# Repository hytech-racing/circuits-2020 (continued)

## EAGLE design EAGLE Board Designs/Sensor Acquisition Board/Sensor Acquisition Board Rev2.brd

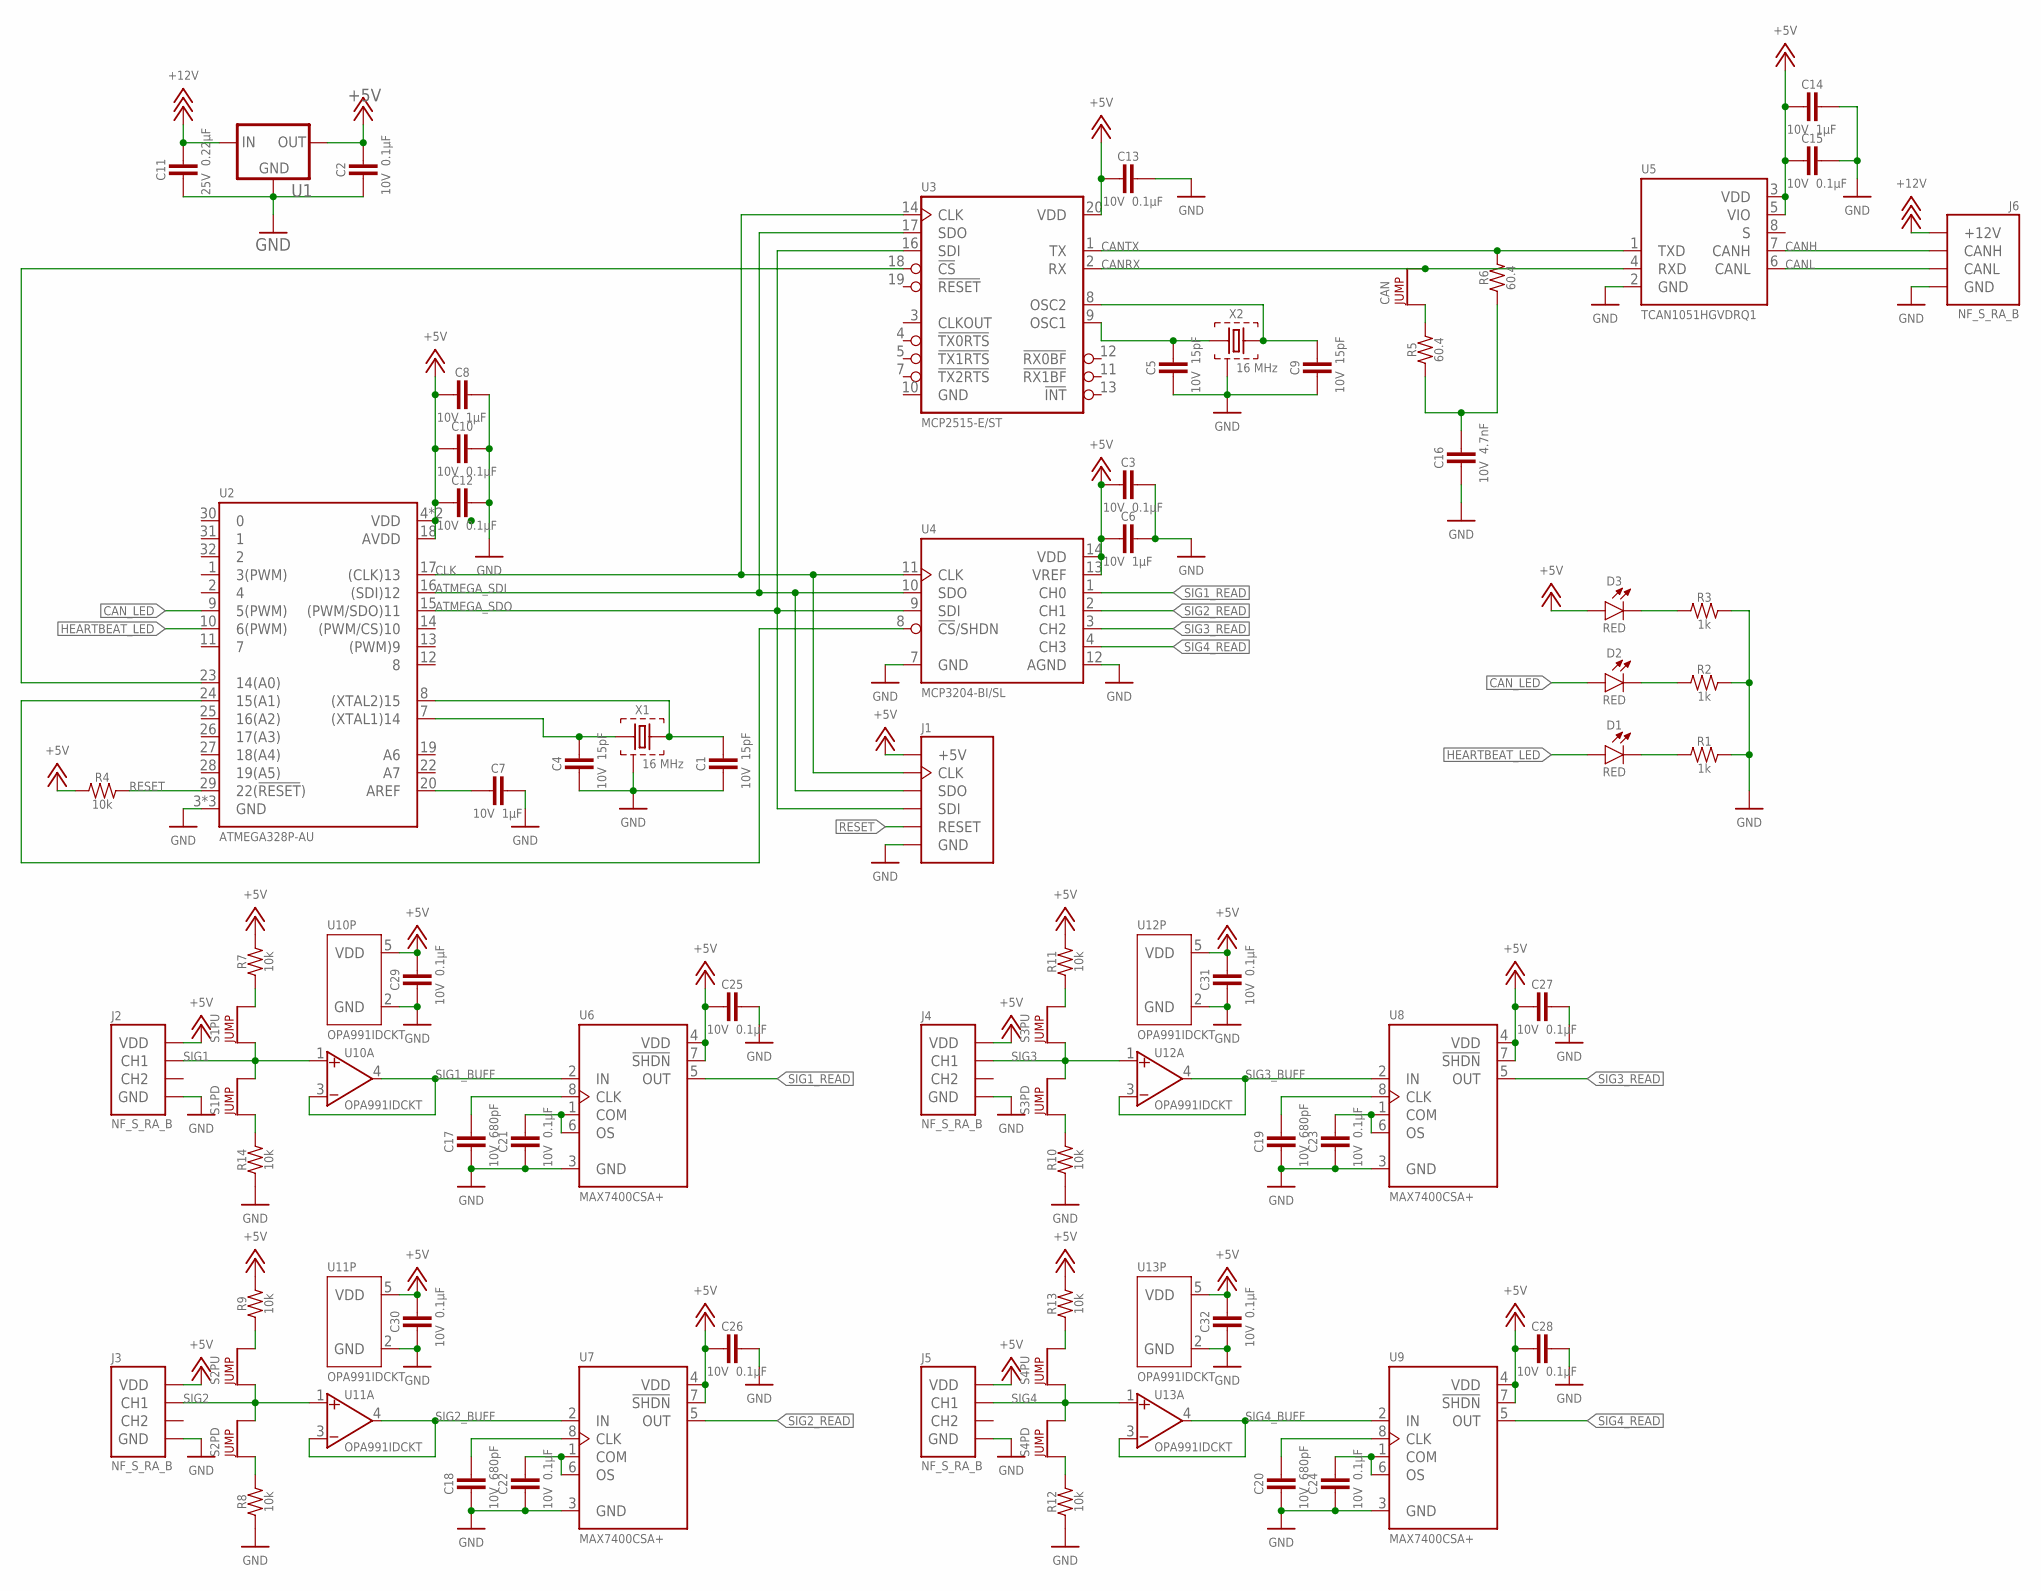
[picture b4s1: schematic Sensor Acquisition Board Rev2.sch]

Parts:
C1, C4, C5, C9: CAPACITOR_0603_10V_15PF; 0603-CAP
C2, C3, C10, C12, C13, C15, C21, C22, C23, C24, C25, C26, C27, C28, C29, C30, C31, C32: CAPACITOR_0603_10V_0.1UF; 0603-CAP
C6, C7, C8, C14: CAPACITOR_0603_10V_1UF; 0603-CAP
C11: CAPACITOR_0603_25V_0.22UF; 0603-CAP
C16: CAPACITOR_0603_10V_4.7NF; 0603-CAP
C17, C18, C19, C20: CAPACITOR_0603_10V_680PF; 0603-CAP
CAN: JUMPER_1X02_; 1X02
D1, D2, D3: LED_0603_RED; 0603-LED
J1: CONNECTOR-AVR-ISP__; 2X03
J2, J3, J4, J5: CONNECTOR-SENSOR_NF_S_RA_BLACK; MOLEX_NANOFIT_SMD_RIGHTANGLE_04
J6: CONNECTOR-CAN_NF_S_RA_BLACK; MOLEX_NANOFIT_SMD_RIGHTANGLE_04
R1, R2, R3: RESISTOR_0603_1K; 0603-RES
R4, R7, R8, R9, R10, R11, R12, R13, R14: RESISTOR_0603_10K; 0603-RES
R5, R6: RESISTOR_0603_60.4; 0603-RES
S1PD, S1PU, S2PD, S2PU, S3PD, S3PU, S4PD, S4PU: JUMPER_1X02_; 1X02
U1: LM340; SOT223
U2: ATMEGA328P-AU; TQFP-32
U3: MCP2515; TSSOP-20
U4: MCP3204; SOIC-14
U5: CAN_TRANSCIEVER_TCAN1051HQV-Q1; SOIC-08
U6, U7, U8, U9: MAX7400; SOIC-08
U10, U11, U12, U13: OPAMP_1_CHANNEL_OPA991; SC-70-5
X1, X2: CRYSTAL16MHZ; ABM3B

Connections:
+5V: C2.1, C3.2, C6.2, C8.2, C10.2, C12.2, C13.2, C14.2, C15.2, C25.2, C26.2, C27.2, C28.2, C29.1, C30.1, C31.1, C32.1, D3.2 (A), J1.2 (+5V), J2.1 (VDD), J3.1 (VDD), J4.1 (VDD), J5.1 (VDD), R4.1, R7.2, R9.2, R11.2, R13.2, U1.3 (OUT), U2.4 (VDD), U2.6 (VDD), U2.18 (AVDD), U3.20 (VDD), U4.13 (VREF), U4.14 (VDD), U5.3 (VDD), U5.5 (VIO), U6.4 (VDD), U6.7 (!SHDN), U7.4 (VDD), U7.7 (!SHDN), U8.4 (VDD), U8.7 (!SHDN), U9.4 (VDD), U9.7 (!SHDN), U10.5 (VDD), U11.5 (VDD), U12.5 (VDD), U13.5 (VDD)
+12V: C11.1, J6.1 (+12V), U1.1 (IN)
ATMEGA_CS: U2.24 (15(A1)), U4.8 (!CS!/SHDN)
ATMEGA_SDI: J1.4 (SDO), U2.16 ((SDI)12), U3.17 (SDO), U4.10 (SDO)
ATMEGA_SDO: J1.1 (SDI), U2.15 ((PWM/SDO)11), U3.16 (SDI), U4.9 (SDI)
CANH: J6.4 (CANH), U5.7 (CANH)
CANL: J6.3 (CANL), U5.6 (CANL)
CANRX: CAN.2, U3.2 (RX), U5.4 (RXD)
CANTX: R6.2, U3.1 (TX), U5.1 (TXD)
CAN_LED: D2.2 (A), U2.9 (5(PWM))
CLK: J1.3 (CLK), U2.17 ((CLK)13), U3.14 (CLK), U4.11 (CLK)
GND: C1.2, C2.2, C3.1, C4.2, C5.2, C6.1, C7.1, C8.1, C9.2, C10.1, C11.2, C12.1, C13.1, C14.1, C15.1, C16.2, C17.2, C18.2, C19.2, C20.2, C21.2, C22.2, C23.2, C24.2, C25.1, C26.1, C27.1, C28.1, C29.2, C30.2, C31.2, C32.2, J1.6 (GND), J2.2 (GND), J3.2 (GND), J4.2 (GND), J5.2 (GND), J6.2 (GND), R1.2, R2.2, R3.2, R8.1, R10.1, R12.1, R14.1, U1.2 (GND), U1.4 (GND), U2.3 (GND), U2.5 (GND), U2.21 (GND), U3.10 (GND), U4.7 (GND), U4.12 (AGND), U5.2 (GND), U6.3 (GND), U7.3 (GND), U8.3 (GND), U9.3 (GND), U10.2 (GND), U11.2 (GND), U12.2 (GND), U13.2 (GND), X1.2 (GND), X1.4 (GND), X2.2 (GND), X2.4 (GND)
HEARTBEAT_LED: D1.2 (A), U2.10 (6(PWM))
unnamed: CAN.1, R5.2
unnamed: C16.1, R5.1, R6.1
unnamed: C17.1, U6.8 (CLK)
unnamed: C21.1, U6.1 (COM), U6.6 (OS)
unnamed: D3.1 (C), R3.1
unnamed: D2.1 (C), R2.1
unnamed: D1.1 (C), R1.1
unnamed: U2.23 (14(A0)), U3.18 (!CS)
unnamed: C5.1, U3.9 (OSC1), X2.1
unnamed: C9.1, U3.8 (OSC2), X2.3
unnamed: C4.1, U2.7 ((XTAL1)14), X1.1
unnamed: C1.1, U2.8 ((XTAL2)15), X1.3
unnamed: C7.2, U2.20 (AREF)
unnamed: R7.1, S1PU.2
unnamed: R14.2, S1PD.1
unnamed: C18.1, U7.8 (CLK)
unnamed: C22.1, U7.1 (COM), U7.6 (OS)
unnamed: R9.1, S2PU.2
unnamed: R8.2, S2PD.1
unnamed: C19.1, U8.8 (CLK)
unnamed: C23.1, U8.1 (COM), U8.6 (OS)
unnamed: R11.1, S3PU.2
unnamed: R10.2, S3PD.1
unnamed: C20.1, U9.8 (CLK)
unnamed: C24.1, U9.1 (COM), U9.6 (OS)
unnamed: R13.1, S4PU.2
unnamed: R12.2, S4PD.1
RESET: J1.5 (RESET), R4.2, U2.29 (22(!RESET!))
SIG1: J2.3 (CH1), S1PD.2, S1PU.1, U10.1 (VIN+)
SIG1_BUFF: U6.2 (IN), U10.3 (VIN-), U10.4 (VOUT)
SIG1_READ: U4.1 (CH0), U6.5 (OUT)
SIG2: J3.3 (CH1), S2PD.2, S2PU.1, U11.1 (VIN+)
SIG2_BUFF: U7.2 (IN), U11.3 (VIN-), U11.4 (VOUT)
SIG2_READ: U4.2 (CH1), U7.5 (OUT)
SIG3: J4.3 (CH1), S3PD.2, S3PU.1, U12.1 (VIN+)
SIG3_BUFF: U8.2 (IN), U12.3 (VIN-), U12.4 (VOUT)
SIG3_READ: U4.3 (CH2), U8.5 (OUT)
SIG4: J5.3 (CH1), S4PD.2, S4PU.1, U13.1 (VIN+)
SIG4_BUFF: U9.2 (IN), U13.3 (VIN-), U13.4 (VOUT)
SIG4_READ: U4.4 (CH3), U9.5 (OUT)

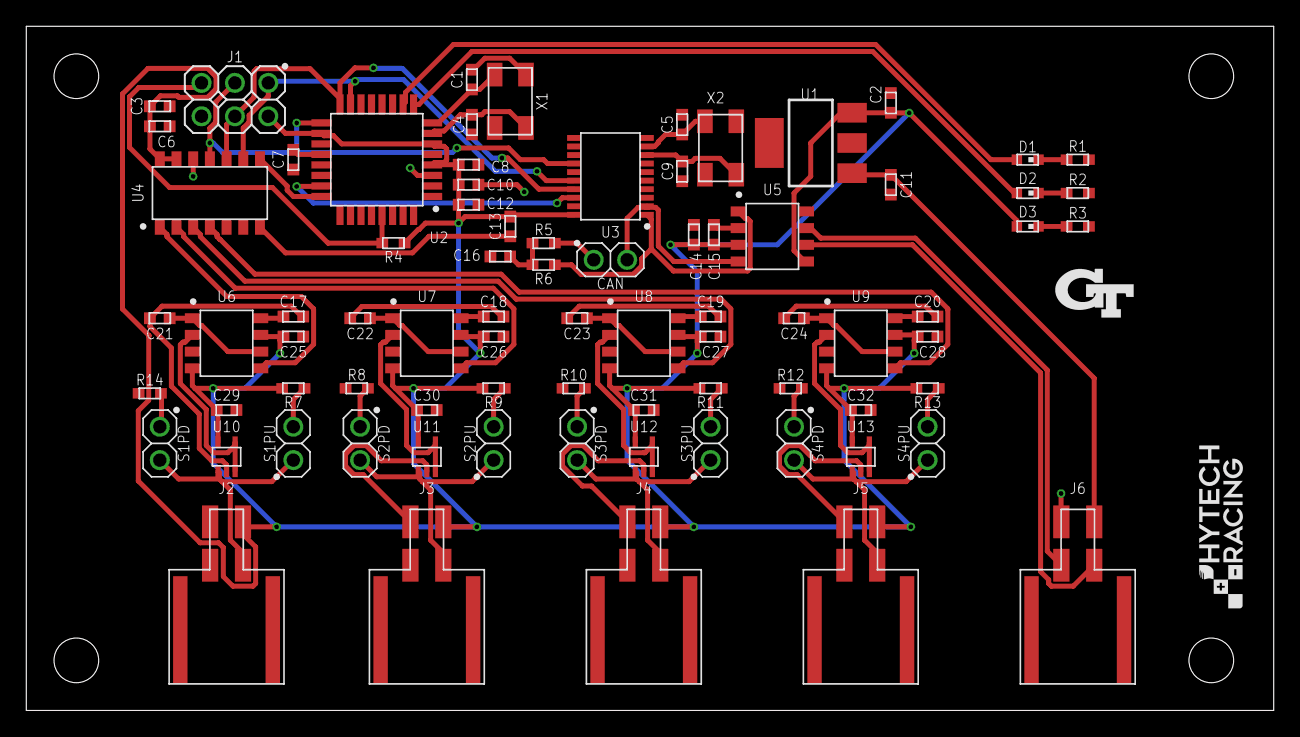
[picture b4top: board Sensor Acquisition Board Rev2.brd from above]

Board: 2 copper layers, 94.9 x 52.1 mm, 85 parts (0 on the bottom side), 53 nets.

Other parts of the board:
U$1, U$2, U$4, U$5: MOUNTING_M3
U$3: LOGO_HYTECH_0.5"
U$6: LOGO_GT_0.25"

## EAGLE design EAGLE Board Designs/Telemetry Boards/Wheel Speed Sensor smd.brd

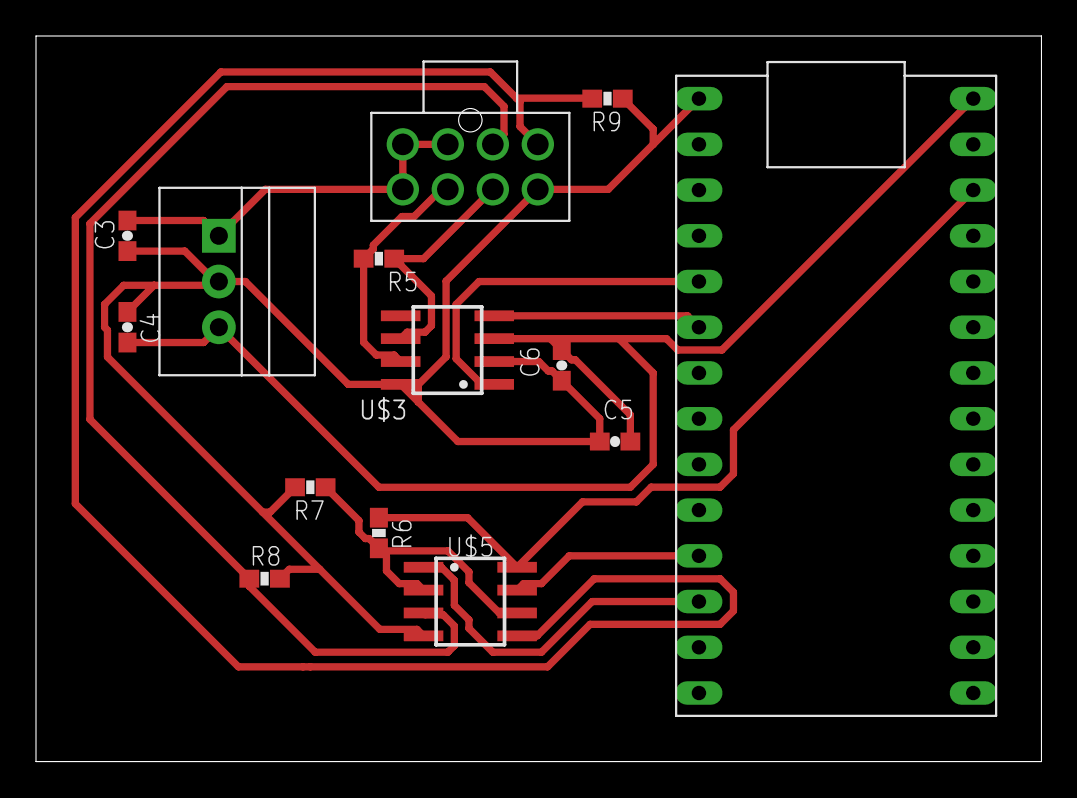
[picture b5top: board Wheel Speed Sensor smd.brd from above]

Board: 2 copper layers, 55.9 x 40.3 mm, 14 parts (0 on the bottom side), 13 nets.

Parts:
C3, C4: 10uF; 0603-CAP
C5: 1uF; 0603-CAP
C6: .1 uF; 0603-CAP
R5: 220; 0603-RES
R6, R7: 1k; 0603-RES
R8, R9: 150; 0603-RES
REG: 5V; OKI-78SR
U$2: TEENSY_3.2_SIMPLE
U$3: MCP2551; SOIC-08
U$5: MCP6002SOIC; SOIC-08
X3: CONNECTOR-8NANO-FIT_VERTICAL-8; NANO-FIT_VERTICAL-8

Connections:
+3V3: R6.1, U$2.3.3V, U$5.8
+5V: C4.2, C5.2, C6.2, REG.3, U$2.VIN, U$3.3
+12V: C3.2, REG.1, X3.P$3, X3.P$4, X3.P$8
CANH: R5.1, U$3.7, X3.P$7
CANL: R5.2, U$3.6, X3.P$6
CANRX: U$2.D4(CANRX), U$3.4
CANTX: U$2.D3(CANTX), U$3.1
GND: C3.1, C4.1, C5.1, C6.1, R7.2, R8.2, R9.1, REG.2, U$2.GND, U$3.2, U$3.8, U$5.4, X3.P$5
unnamed: R6.2, R7.1, U$5.2, U$5.6
WS1: U$2.D10(TX2), U$5.1
WS1_OUT: R8.1, U$5.3, X3.P$2
WS2: U$2.D9(RX2), U$5.7
WS2_OUT: R9.2, U$5.5, X3.P$1

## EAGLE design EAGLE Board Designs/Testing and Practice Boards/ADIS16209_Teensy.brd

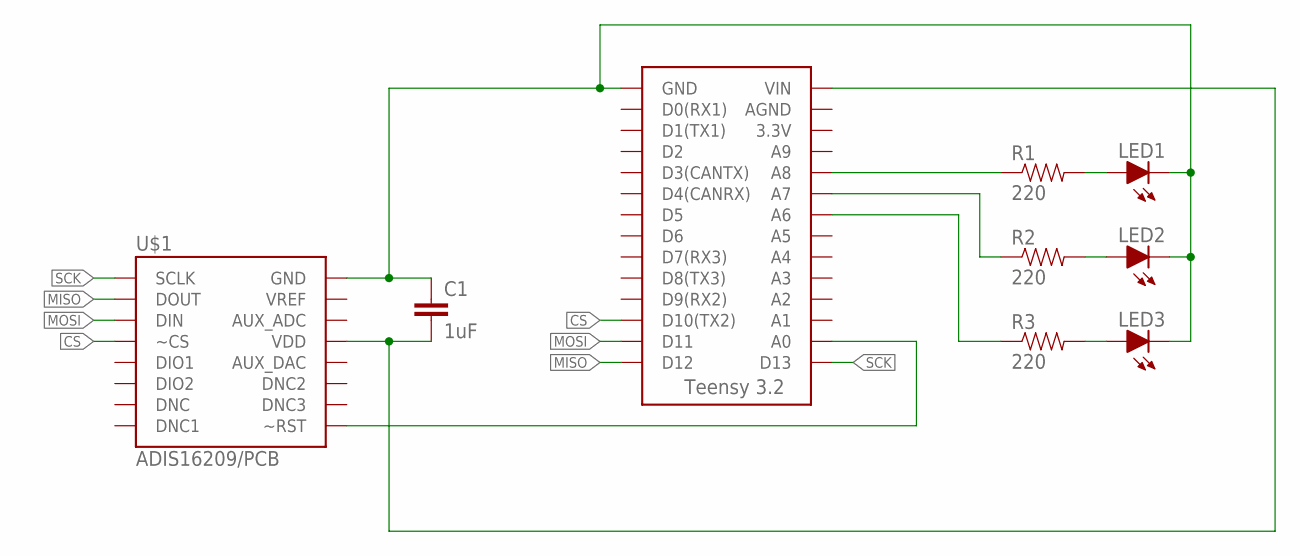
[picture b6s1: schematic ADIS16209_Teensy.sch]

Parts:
C1: 1uF; CAP-PTH-SMALL-KIT
LED1, LED2, LED3: LED-5MM
R1, R2, R3: 220; AXIAL-0.4
U$1: ADIS16209/PCB
U$2: TEENSY_3.2_SIMPLE

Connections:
+3V3: C1.2, U$1.P$10 (VDD), U$1.P$11 (VDD), U$1.P$12 (VDD), U$2.VIN
CS: U$1.P$3 (~CS), U$2.D10(TX2)
GND: C1.1, LED1.K (C), LED2.K (C), LED3.K (C), U$1.P$7 (GND), U$1.P$8 (GND), U$1.P$14 (GND), U$1.P$17 (GND), U$2.GND
MISO: U$1.P$4 (DOUT), U$2.D12
MOSI: U$1.P$6 (DIN), U$2.D11
unnamed: LED1.A, R1.P$2 (2)
unnamed: U$1.P$1 (~RST), U$2.A0
unnamed: R1.P$1 (1), U$2.A8
unnamed: R2.P$1 (1), U$2.A7
unnamed: R3.P$1 (1), U$2.A6
unnamed: LED2.A, R2.P$2 (2)
unnamed: LED3.A, R3.P$2 (2)
SCK: U$1.P$2 (SCLK), U$2.D13

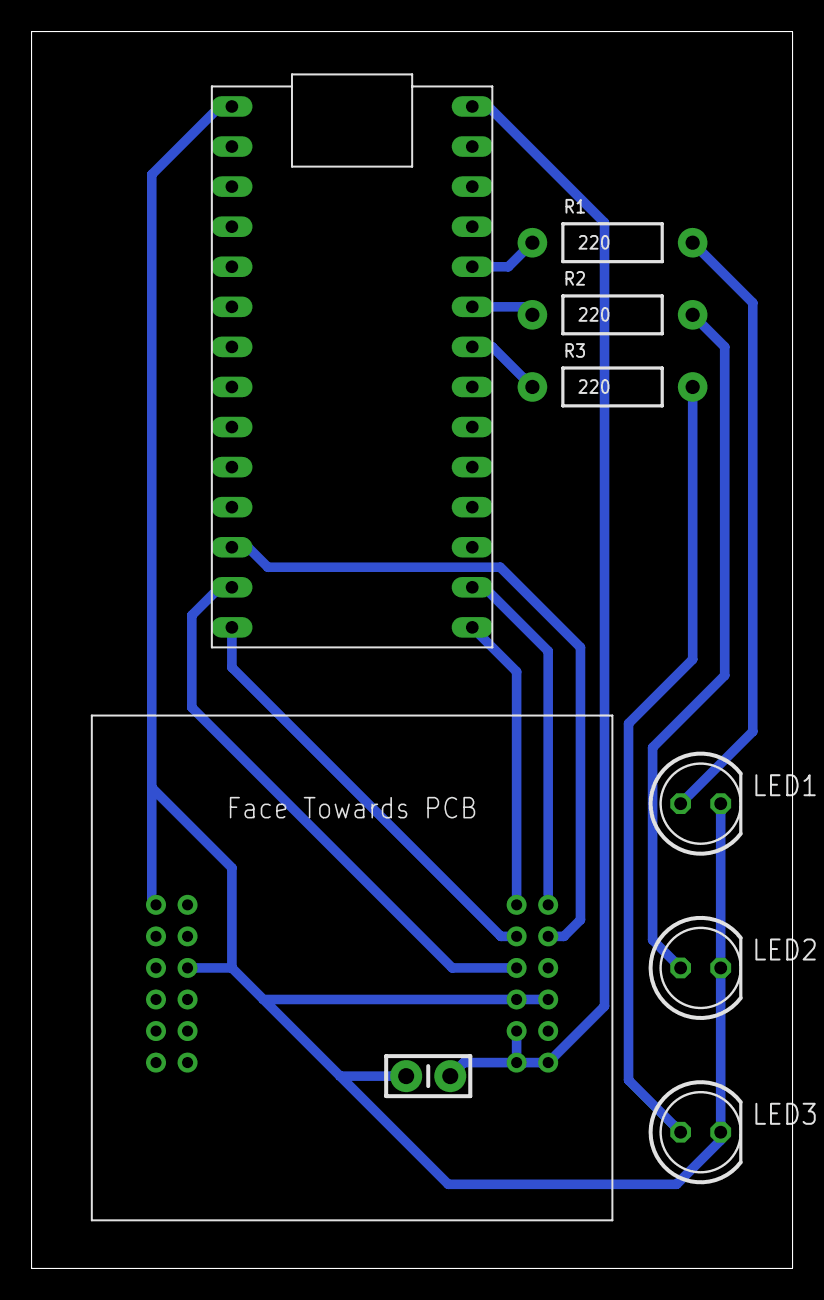
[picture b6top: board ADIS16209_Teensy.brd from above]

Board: 2 copper layers, 48.2 x 78.4 mm, 9 parts (0 on the bottom side), 13 nets.

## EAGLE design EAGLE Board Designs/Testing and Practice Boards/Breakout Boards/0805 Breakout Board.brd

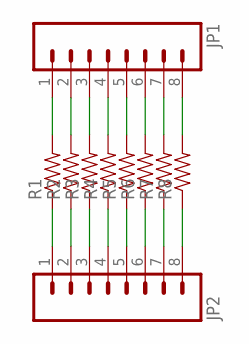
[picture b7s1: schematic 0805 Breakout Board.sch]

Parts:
JP1, JP2: M08; 1X08
R1, R2, R3, R4, R5, R6, R7, R8: RESISTOR0805-RES; 0805

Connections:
unnamed: JP1.1, R1.2
unnamed: JP2.8, R8.1
unnamed: JP2.7, R7.1
unnamed: JP1.2, R2.2
unnamed: JP2.6, R6.1
unnamed: JP1.3, R3.2
unnamed: JP2.5, R5.1
unnamed: JP1.4, R4.2
unnamed: JP1.5, R5.2
unnamed: JP2.4, R4.1
unnamed: JP2.3, R3.1
unnamed: JP1.6, R6.2
unnamed: JP1.7, R7.2
unnamed: JP2.2, R2.1
unnamed: JP2.1, R1.1
unnamed: JP1.8, R8.2

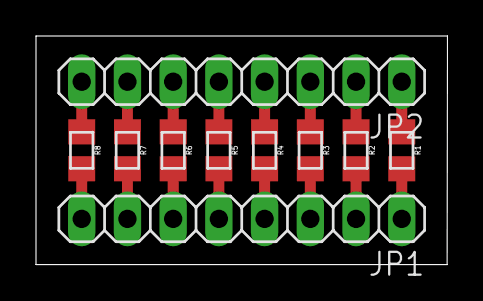
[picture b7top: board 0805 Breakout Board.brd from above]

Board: 2 copper layers, 22.9 x 12.7 mm, 10 parts (0 on the bottom side), 16 nets.
